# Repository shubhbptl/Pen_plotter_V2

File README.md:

# Pen Plotter
### MHS/MVTHS Robotics and Enginering                
##### By: Shubh Patel, Roman Rice
---------------
# Requirement
```python
pip install -r requirements.txt
python3 -m pip install --user pipx
python3 -m pipx ensurepath
pipx install vpype\
&& pipx inject vpype hatched\
&& pipx inject vpype vpype-gcode
mv ./bundled_configs.toml /root/.local/share/pipx/venvs/vpype/lib/python3.9/site-packages/vpype_gcode/bundled_configs.toml
vpype -c /root/.local/share/pipx/venvs/vpype/lib/python3.9/site-packages/vpype_gcode/bundled_configs.toml
``` 
# Installation Guide

##  Step 1: change line of code #114 and #139 in Main.py
change to
```python
processing_url = "Your_Processing_Server_Ip/process"
```
your Ip address that your running your server on
Ex:
```python
processing_url = "10.1.57.108/process"
```
## Line 122 in processing_server.py
change to
```python
main_url = "Main_Server_URL/retrive"
```
your Ip address that your running your server on
Ex:
```python
main_url = "10.1.57.108/retrive"
```

## Step 2: Start the Main Server
First, start the main server by navigating to the Main_Server directory and running the main Python script.
```python3
python3 /Main_Server/main.py
```
## Important Step 3: Start the Processing Server, if you dont start this server Img won't be able to convert to gcode
Next, start the processing server by navigating to the Processing_Server/Server directory and running the processing server script.
```python3
python3 /Processing_Server/Processing_Server/processing_server.py
```
## Utilization

1. Upload a file to the pen plotter server.
2. Preview the generated gcode.
3. Home the pen plotter.
4. load new paper 
5. Print!

# Important note 
## Emergency button 
If the prints fails to print or excceds print boundries.This will reset the Arduino and home itself.
## Reset-Alaram
Resets Grbl software and sets all the limits switch to idle. Only use this if the prints stop while running or Run out of boundries.
## Paper_Roller on & Off
This will allow you to turn on and off paper-Roller motor manually.
## Homing
This will home the pen to its origin.
## Print
This will print the current sketch from the /Main_Server/static/Image_Storage/Gcodes folder

# How everything works!
## img convert to gcode
The img user uploads get send to Processing Server which is build with flask, Img then get processed using library called Vpype which converts Img to gcode. The Processing Server send back the gcode of the img.

## Print the Gcode
For reading the gcode and printing it on paper. I'm using Grbl which is the backend of the pen-plotter. It only takes in Gcode. The Grbl firmware is uploaded into Metro-Mini. Raspberry Pi is connected to Metro-Mini through Uart Communication. Only job of Metro-Mini has to do is excute the gcode send by Raspberry pi.

## About This Project

This project was started by Shubh Patel during the 2022-2023 school year at the [Robotics and Engineering](https://mvthsengineering.com/) program of the [Medford Vocational Technical High School](https://mhs-mvths.mps02155.org/). It is currently still under active development.

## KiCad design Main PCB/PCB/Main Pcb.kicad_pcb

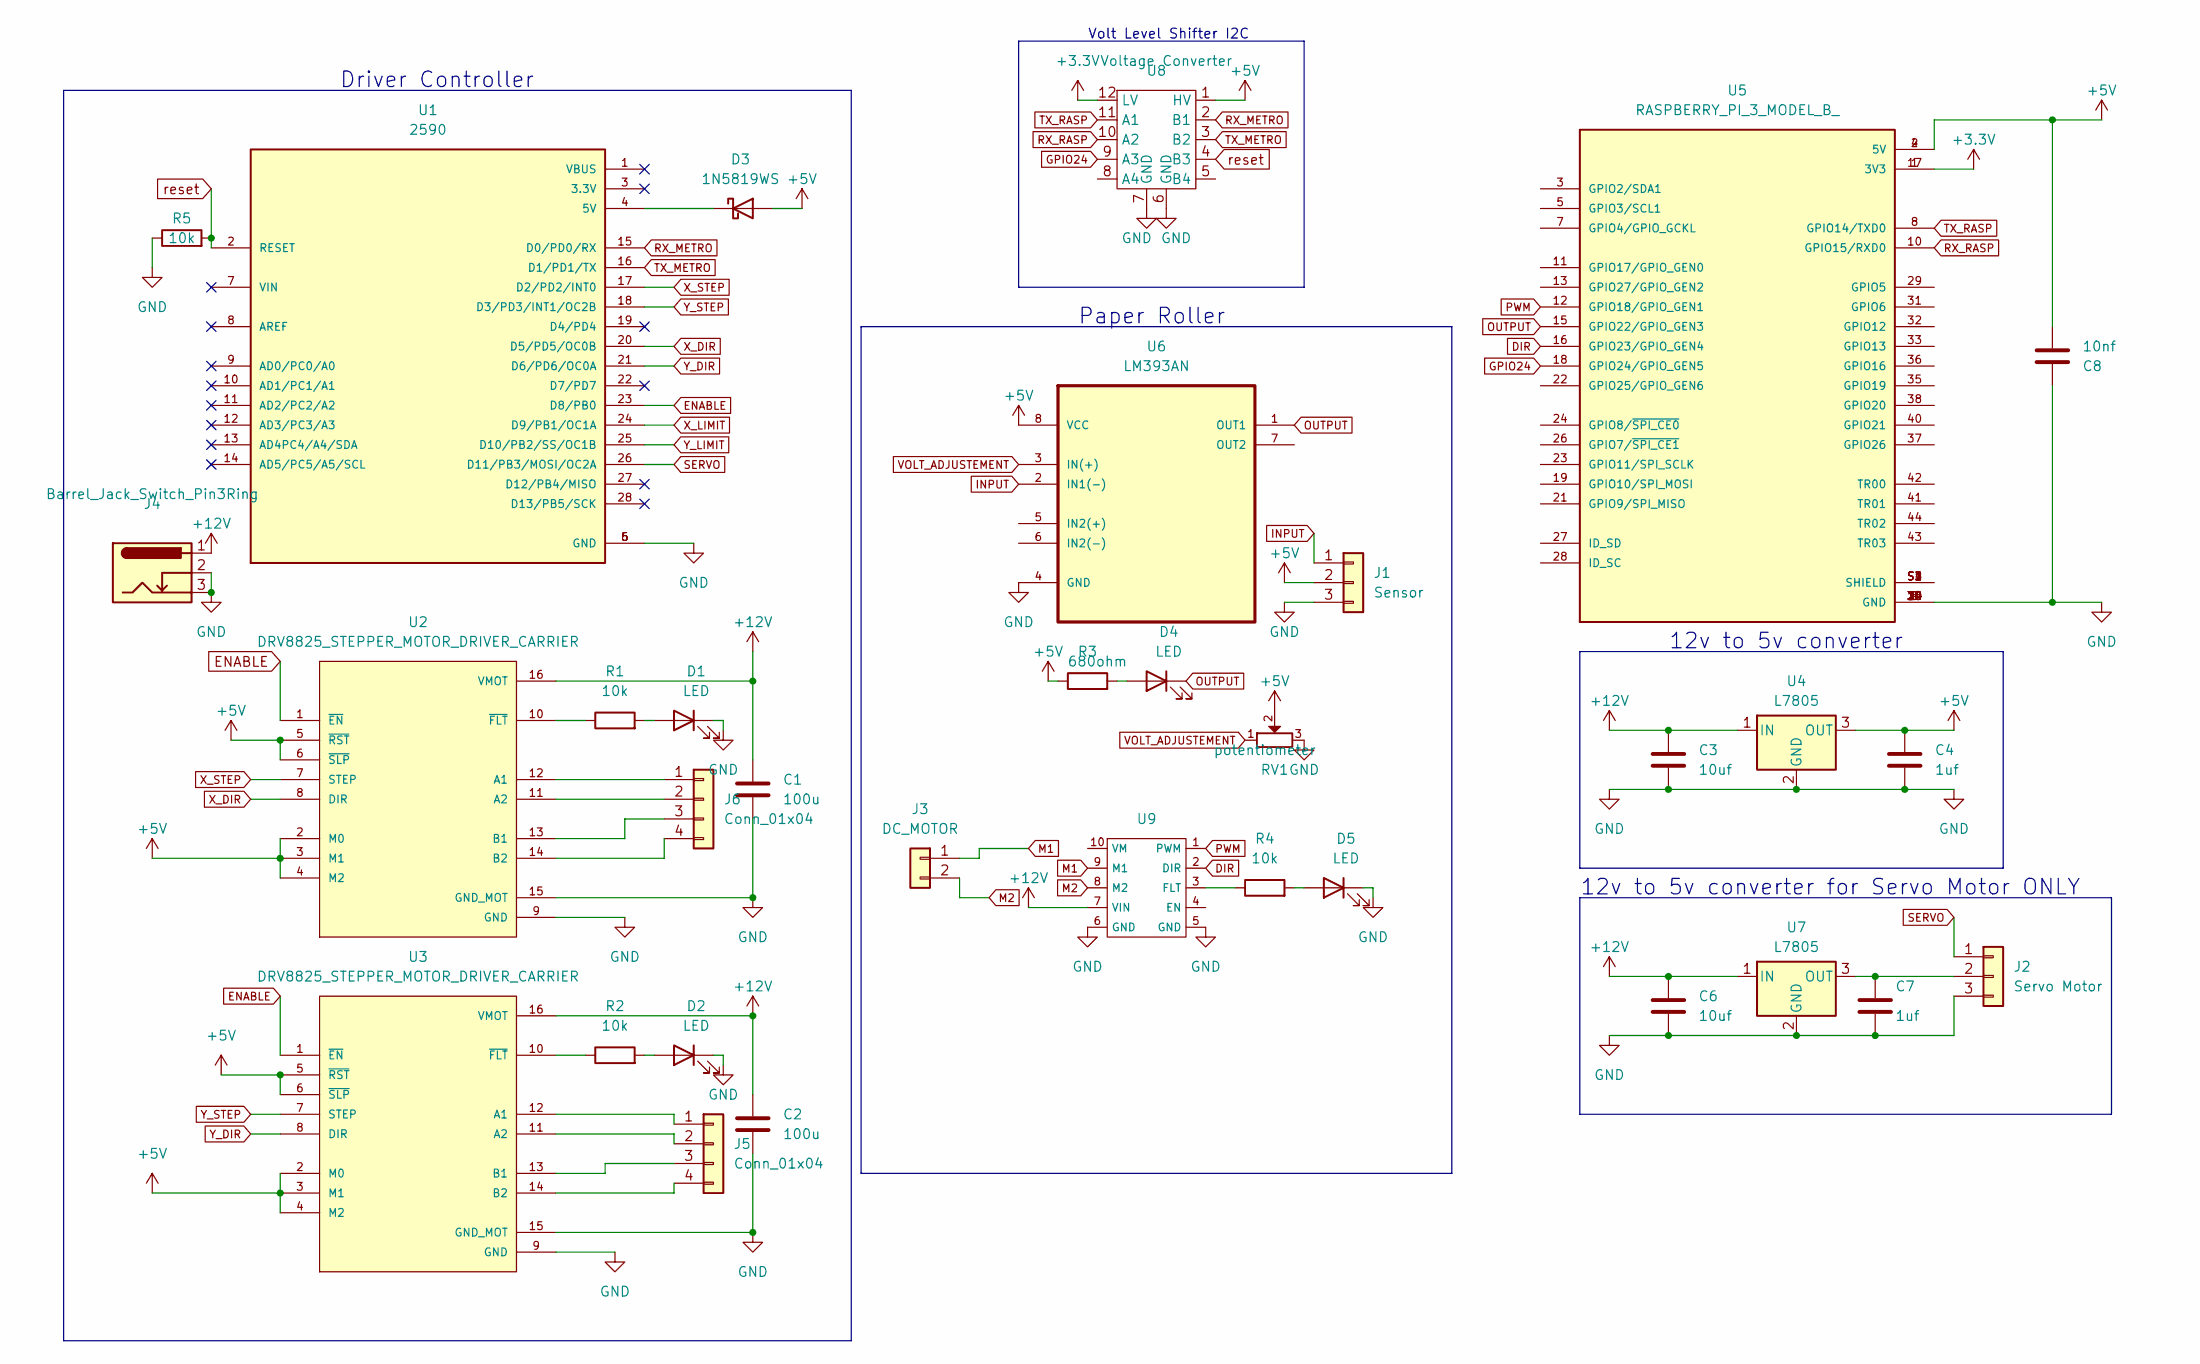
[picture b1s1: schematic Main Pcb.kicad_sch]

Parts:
C1, C2: 100u
C3, C6: 10uf; 100u
C4, C7: 1uf; 100u
C8: 10nf; 100u
D1, D2, D4, D5: LED; LED_D3.0mm
D3: 1N5819WS; D_DO-15_P10.16mm_Horizontal
J1: Sensor; PinSocket_1x03_P2.54mm_Horizontal
J2: Servo Motor; PinSocket_1x03_P2.54mm_Vertical
J3: DC_MOTOR; PinSocket_2x01_P2.54mm_Vertical
J4: Barrel_Jack_Switch_Pin3Ring; BarrelJack_Kycon_KLDX-0202-xC_Horizontal
J5, J6: Conn_01x04; PinHeader_1x04_P2.54mm_Horizontal
R1, R2, R4, R5: 10k; 100u
R3: 680ohm; 100u
RV1: potentiometer; potentiometer_3362P
U1: 2590; Metro Mini; PARTREV N/A
U2, U3: DRV8825_STEPPER_MOTOR_DRIVER_CARRIER; DRV8825
U4, U7: L7805
U5: RASPBERRY_PI_3_MODEL_B_; PARTREV N/A
U6: LM393AN
U8: Voltage Converter; VOLTAGE LEVEL SHIFTER CONVERTER
U9: DC_MOTOR_DRIVER

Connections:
+3.3V: U5.1 (3V3), U5.17 (3V3), U8.12 (LV)
+5V: C4.1, C8.2, D3.2 (A), J1.2, R3.1, RV1.2, U2.2 (M0), U2.3 (M1), U2.4 (M2), U2.5 (~RST), U2.6 (~SLP), U3.2 (M0), U3.3 (M1), U3.4 (M2), U3.5 (~RST), U3.6 (~SLP), U4.3 (OUT), U5.2 (5V), U5.4 (5V), U6.8 (VCC), U8.1 (HV); also elsewhere on the board
+12V: C1.1, C2.1, C3.1, C6.1, J4.1, U2.16 (VMOT), U3.16 (VMOT), U4.1 (IN), U7.1 (IN), U9.7 (VIN)
DIR: U5.16 (GPIO23/GPIO_GEN4), U9.2 (DIR)
ENABLE: U1.23 (D8/PB0), U2.1 (~EN), U3.1 (~EN)
GND: C1.2, C2.2, C3.2, C4.2, C6.2, C7.2, C8.1, D1.1 (K), D2.1 (K), D5.1 (K), J1.3, J2.3, J4.2, J4.3, R5.1, RV1.3, U1.5 (GND), U1.6 (GND), U2.9 (GND), U2.15 (GND_MOT), U3.9 (GND), U3.15 (GND_MOT), U4.2 (GND), U5.6 (GND), U5.9 (GND), U5.14 (GND), U5.20 (GND), U5.25 (GND), U5.30 (GND), U5.34 (GND), U5.39 (GND), U6.4 (GND), U7.2 (GND), U8.6 (GND), U8.7 (GND), U9.5 (GND), U9.6 (GND)
GPIO24: U5.18 (GPIO24/GPIO_GEN5), U8.9 (A3)
INPUT: J1.1, U6.2 (IN1(-))
M1: J3.1, U9.9 (M1)
M2: J3.2, U9.8 (M2)
unnamed: D1.2 (A), R1.2
unnamed: D2.2 (A), R2.2
unnamed 12: D3.1 (K), U1.4 (5V); also elsewhere on the board
unnamed: D4.2 (A), R3.2
unnamed: D5.2 (A), R4.2
unnamed: C7.1, J2.2, U7.3 (OUT)
unnamed: J5.1, U3.12 (A1)
unnamed: J5.2, U3.11 (A2)
unnamed: J5.3, U3.13 (B1)
unnamed: J5.4, U3.14 (B2)
unnamed: J6.1, U2.12 (A1)
unnamed: J6.2, U2.11 (A2)
unnamed: J6.3, U2.13 (B1)
unnamed: J6.4, U2.14 (B2)
unnamed: R1.1, U2.10 (~FLT)
unnamed: R2.1, U3.10 (~FLT)
unnamed: U5.S1 (SHIELD), U5.S2 (SHIELD), U5.S3 (SHIELD), U5.S4 (SHIELD)
unnamed: R4.1, U9.3 (FLT)
OUTPUT: D4.1 (K), U5.15 (GPIO22/GPIO_GEN3), U6.1 (OUT1)
PWM: U5.12 (GPIO18/GPIO_GEN1), U9.1 (PWM)
RX_METRO: U1.15 (D0/PD0/RX), U8.2 (B1)
RX_RASP: U5.10 (GPIO15/RXD0), U8.10 (A2)
SERVO: J2.1, U1.26 (D11/PB3/MOSI/OC2A)
TX_METRO: U1.16 (D1/PD1/TX), U8.3 (B2)
TX_RASP: U5.8 (GPIO14/TXD0), U8.11 (A1)
VOLT_ADJUSTEMENT: RV1.1, U6.3 (IN(+))
X_DIR: U1.20 (D5/PD5/OC0B), U2.8 (DIR)
X_LIMIT: U1.24 (D9/PB1/OC1A)
X_STEP: U1.17 (D2/PD2/INT0), U2.7 (STEP)
Y_DIR: U1.21 (D6/PD6/OC0A), U3.8 (DIR)
Y_LIMIT: U1.25 (D10/PB2/SS/OC1B)
Y_STEP: U1.18 (D3/PD3/INT1/OC2B), U3.7 (STEP)
reset: R5.2, U1.2 (RESET), U8.4 (B3)

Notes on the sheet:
12v to 5v converter
Volt Level Shifter I2C
Driver Controller
12v to 5v converter for Servo Motor ONLY
Paper Roller

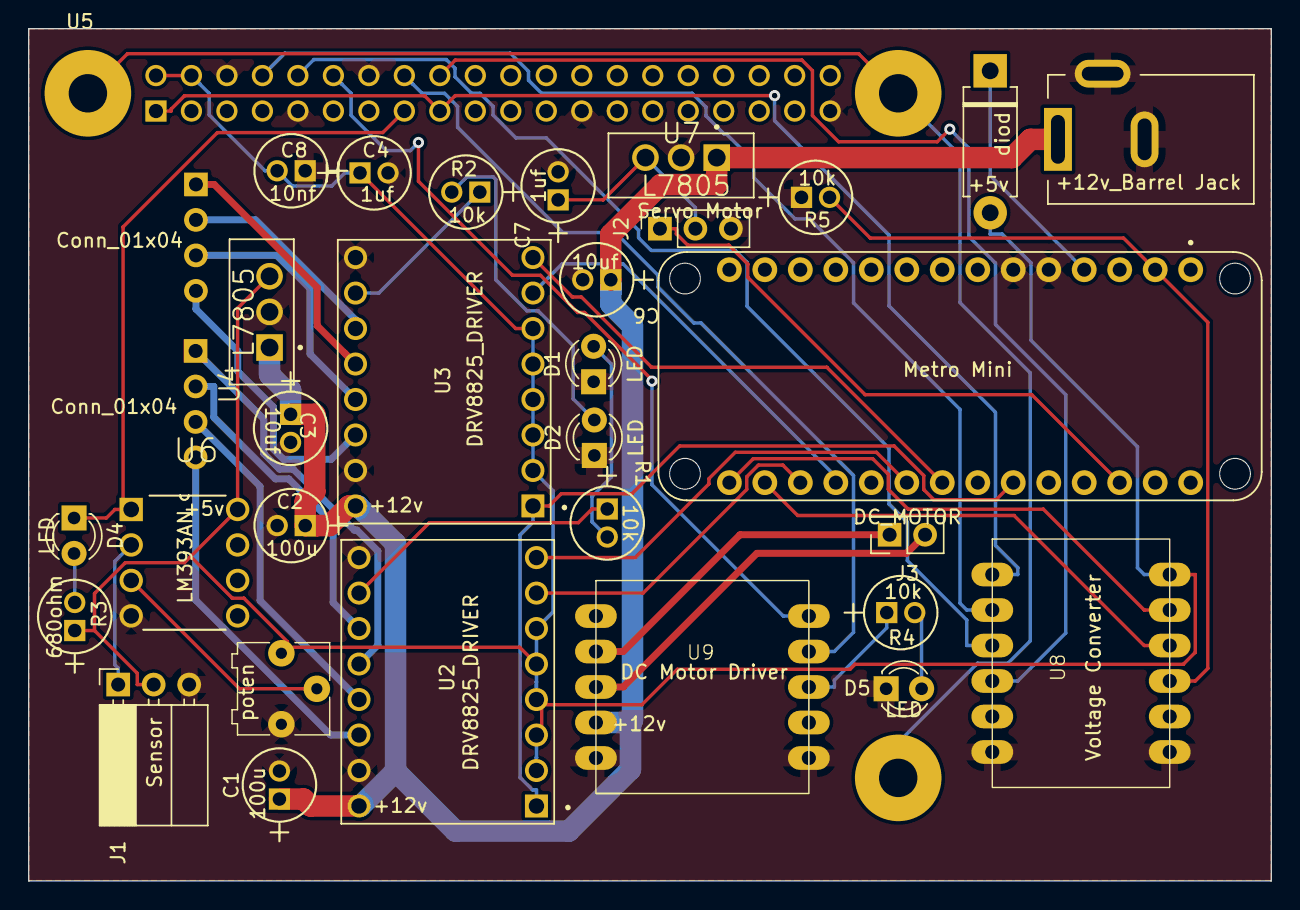
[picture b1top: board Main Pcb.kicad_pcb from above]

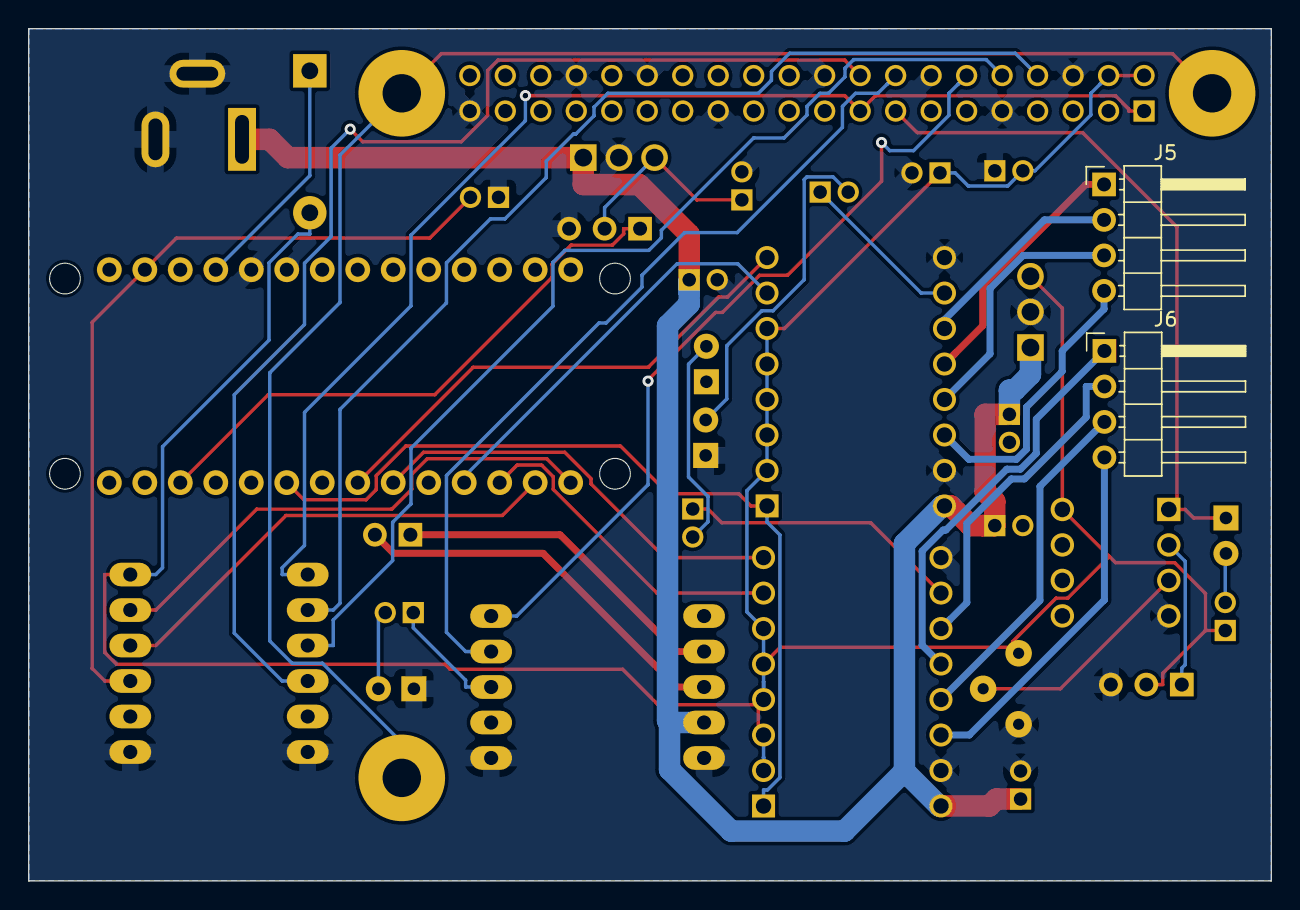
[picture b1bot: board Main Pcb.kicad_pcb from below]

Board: 2 copper layers, 89.0 x 61.0 mm, 33 parts (2 on the bottom side), 41 nets.

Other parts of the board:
+5v: diod; D_DO-15_P10.16mm_Horizontal

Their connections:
+5V: +5v.2 (A); also elsewhere on the board
unnamed 12: +5v.1 (K); also elsewhere on the board

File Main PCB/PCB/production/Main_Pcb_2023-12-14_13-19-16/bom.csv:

Designator,Footprint,Quantity,Value,LCSC Part #
"C1, C2",100u,2,100u,
"C3, C6",100u,2,10uf,
"C4, C7",100u,2,1uf,
C8,100u,1,10nf,
"D1, D2, D4, D5",LED_D3.0mm,4,LED,
D3,D_DO-15_P10.16mm_Horizontal,1,diod,
J1,PinSocket_1x03_P2.54mm_Horizontal,1,Sensor ,
J2,PinSocket_1x03_P2.54mm_Vertical,1,Servo Motor,
J3,PinSocket_2x01_P2.54mm_Vertical,1,DC_MOTOR,
J4,BarrelJack_Kycon_KLDX-0202-xC_Horizontal,1,+12v_Barrel Jack,
"J5, J6",PinHeader_1x04_P2.54mm_Horizontal,2,Conn_01x04,
"R1, R2, R4, R5",100u,4,10k,
R3,100u,1,680ohm,
RV1,potentiometer_3362P,1,poten,
U1,Metro Mini,1,2590,
"U2, U3",DRV8825,2,DRV8825_DRIVER,
"U4, U7",L7805,2,L7805,
U5,RASPBERRY_PI_3_MODEL_B_,1,RASPBERRY_PI_3_MODEL_B_,
U6,LM393AN,1,LM393AN,
U8,VOLTAGE LEVEL SHIFTER CONVERTER,1,Voltage Converter,
U9,DC_MOTOR_DRIVER,1,~,

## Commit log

2023-05-10 add remove previous images
2023-05-10 remove previous image first
2023-05-12 experiment with adding logo on every print
2023-05-14 vpype and edit svg and create gcode
2023-05-15 vpype text and change main.py
2023-05-15 error fixed
2023-05-16 add text gcode to main.py
2023-05-18 clean the code
2023-05-19 fix print, alarm, and homing
2023-09-20 Very unorganized commit, will not happen again.
2023-09-27 add two folder gcodes and Images
    This folder stores images that were uploaded through server and output gcode which will be saved in Gcodes folder
2023-09-30 Moved body of html into a seperate file.
2023-09-30 Format html.
2023-09-30 Moved script imports into index.html. Removed unused code and html.
2023-09-30 Removed many completely unnecessary script and stylesheet imports.
2023-09-30 Changed website to use updated and stable version of bootstrap.
2023-09-30 Removed styling via css and replaced with using bootstrap.
2023-09-30 Removed unnecessary html tag and renamed general pen plotter control buttons.
2023-09-30 Added a README.md file.
2023-09-30 Deleted now unused css folder from static files.
2023-09-30 Remove old and unused javascript. Added a new proof of concept javascript file.
2023-09-30 Fixed formatting.
2023-09-30 Added a simple markdown renderer to the page.
2023-10-01 Changed buttons on website to submit forms.
2023-10-01 Added a gcode preview window to main page.
2023-10-01 Improved website formatting around gcode preview.
2023-10-01 Improved formatting by allocating more space to preview.
2023-10-01 Made gcode preview display paths correctly.
2023-10-01 Changed gcode upload from drag and drop to file input.
2023-10-01 Added functionality to input img files and automatically scale them.
2023-10-01 Removed unnecessary logging.
2023-10-01 Added template for handler functions, unintentionally fixed a bug which caused img to update all the time forever after selecting an image file.
2023-10-02 Added clarifications to further changes which may need to be made.
2023-10-02 change the software for image to gcode, now using svg2gcode
2023-10-03 new image to svg software
2023-10-04 gcode uploaded can be use to upload file and convert to gcode
2023-10-07 Update main.py
    change png to svg using imagemagick without progressbar
    need to be tested in raspberry pi for perfomance
2023-10-12 change in upload button, and pdf is working
2023-10-16 Create LICENSE
2023-10-19 added feature, so it load logo gcode on top of current gcode
2023-11-06 working all the controlling button and can function
2023-12-08 Add files via upload
    added Paper Roller, Volt level Shifter I2C, 12v to 5v Converter, Reset Switch, and wired raspberry pi
2023-12-14 Add files via upload
    added all parts needed for the PenPlotter. PCB Design and Routing done.
2023-12-29 migrate file to my_flask
2024-01-08 updated main.py, added auto cented gcode
2024-01-08 updated main.py added different style gcode
2024-01-08 not necessary
2024-01-16 working on Docker
2024-01-16 Created semi-functional docker image creation with 'server.sh'
    Docker image still has problems with absolute paths
2024-01-16 added start and stop bash file to run the server
2024-01-18 got installation working on docker, also using pipx to install library
2024-01-18 uncomment run.sh file
2024-01-18 added pdftocairo and fixed vpype config not updating
2024-03-25 updated flask server, transfer processing to another computer
2024-04-04 manuel paper roller buttons, working singleline font
2024-04-29 implemented paper roller into print function
2024-05-28 completed project, things that can be improved is auto center single line font
2024-05-28 Need to run this server with main.py server
    This server converts img into gcodes and sends it back to main server.
2024-05-29 Update processing_server.py
    change line 122 to your main server ip
2024-05-29 Update Dockerfile
